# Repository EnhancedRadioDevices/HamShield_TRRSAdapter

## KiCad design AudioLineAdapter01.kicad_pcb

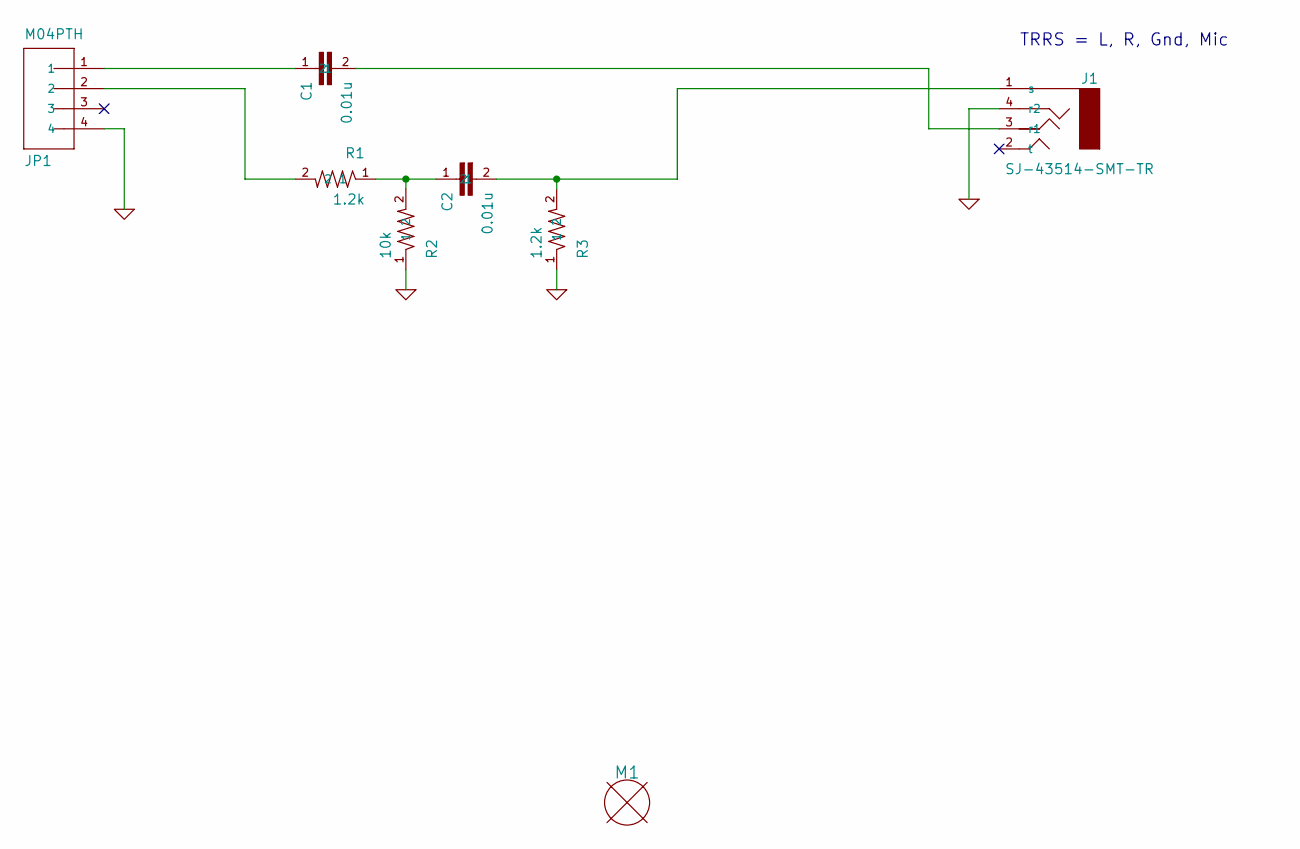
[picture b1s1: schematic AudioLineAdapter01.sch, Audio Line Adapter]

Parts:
C1, C2: 0.01u; C_Disc_D6_P5
J1: SJ-43514-SMT-TR
JP1: M04PTH; SparkFun-1X04
M1: MOUNT_M3; MountingHole_3.2mm_M3
R1, R3: 1.2k; Resistor_Horizontal_RM10mm
R2: 10k; Resistor_Horizontal_RM10mm

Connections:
GND: J1.4 (r2), JP1.4, R2.1, R3.1
unnamed: C1.1, JP1.1
unnamed: C1.2, J1.3 (r1)
unnamed: C2.1, R1.1, R2.2
unnamed: C2.2, J1.1 (s), R3.2
unnamed: JP1.2, R1.2

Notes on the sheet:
TRRS = L, R, Gnd, Mic

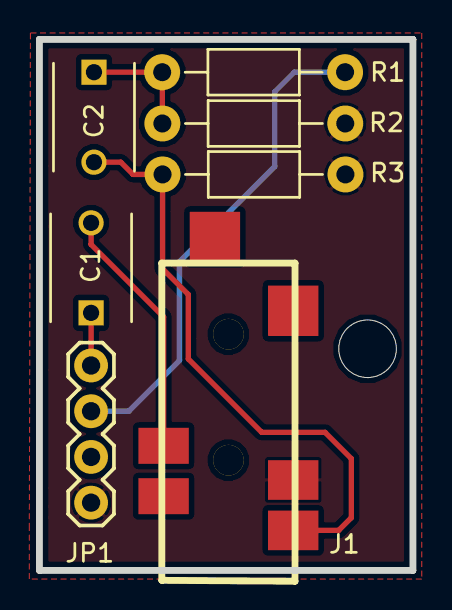
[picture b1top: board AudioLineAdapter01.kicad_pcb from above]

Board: 2 copper layers, 20.8 x 29.5 mm, 8 parts (0 on the bottom side), 6 nets.

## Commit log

2017-09-09 add hw files
